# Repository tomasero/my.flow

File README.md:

#my.flow

###Software
- Arduino sketch adapted for RFduino

###Hardware
- Eagle
	- RFduino shield
	- Magnetic connector plates
- 3D
	- Magnetic connector casing

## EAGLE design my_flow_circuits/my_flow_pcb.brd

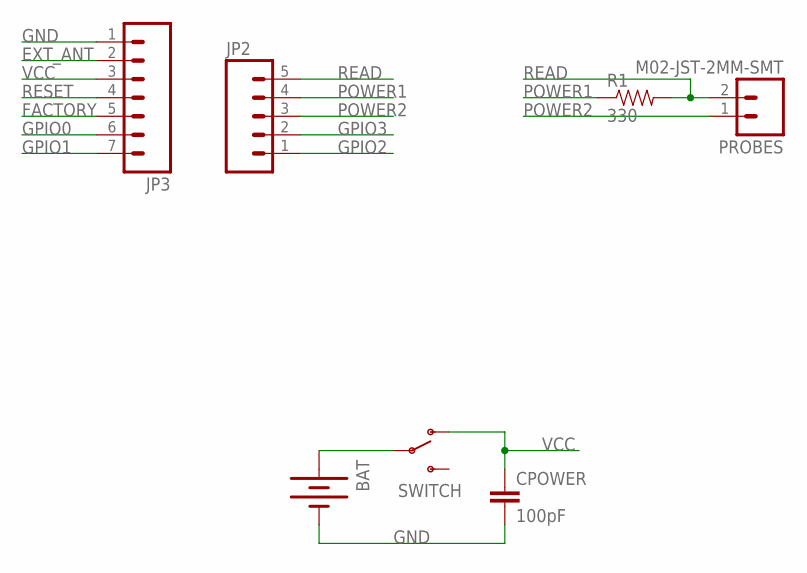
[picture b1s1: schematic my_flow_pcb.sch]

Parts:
BAT: BATTERY12MM; BATTCON_12MM
CPOWER: 100pF; 0805
JP2: M05PTH; 1X05
JP3: M07; 1X07
PROBES: M02-JST-2MM-SMT; JST-2-SMD
R1: 330; 0805
SWITCH: SWITCH-SPDT-SMD-A; SWITCH-SPST-SMD-A

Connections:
BAT+: BAT.PWR@1 (+), SWITCH.2
EXT_ANT: JP3.2
FACTORY: JP3.5
GND: BAT.GND (-), CPOWER.2, JP3.1
GPIO0: JP3.6
GPIO1: JP3.7
GPIO2: JP2.1
GPIO3: JP2.2
POWER1: JP2.4, R1.1
POWER2: JP2.3, PROBES.1 (2)
READ: JP2.5, PROBES.2 (1), R1.2
RESET: JP3.4
VCC: CPOWER.1, JP3.3, SWITCH.1 (O)

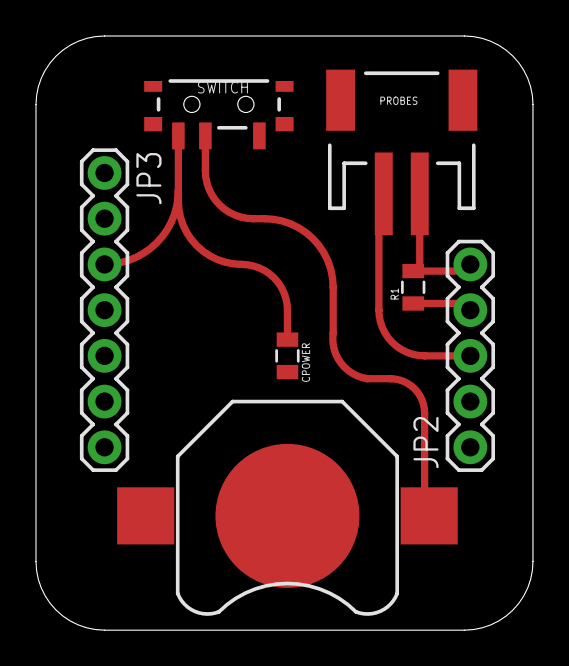
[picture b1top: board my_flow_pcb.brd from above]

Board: 2 copper layers, 27.6 x 33.0 mm, 7 parts (0 on the bottom side), 6 nets.

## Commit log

2015-05-11 clean

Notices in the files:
parts and their libraries:
SparkFun-Connectors: Licensing: Creative Commons ShareAlike 4.0 International - https://creativecommons.org/licenses/by-sa/4.0
